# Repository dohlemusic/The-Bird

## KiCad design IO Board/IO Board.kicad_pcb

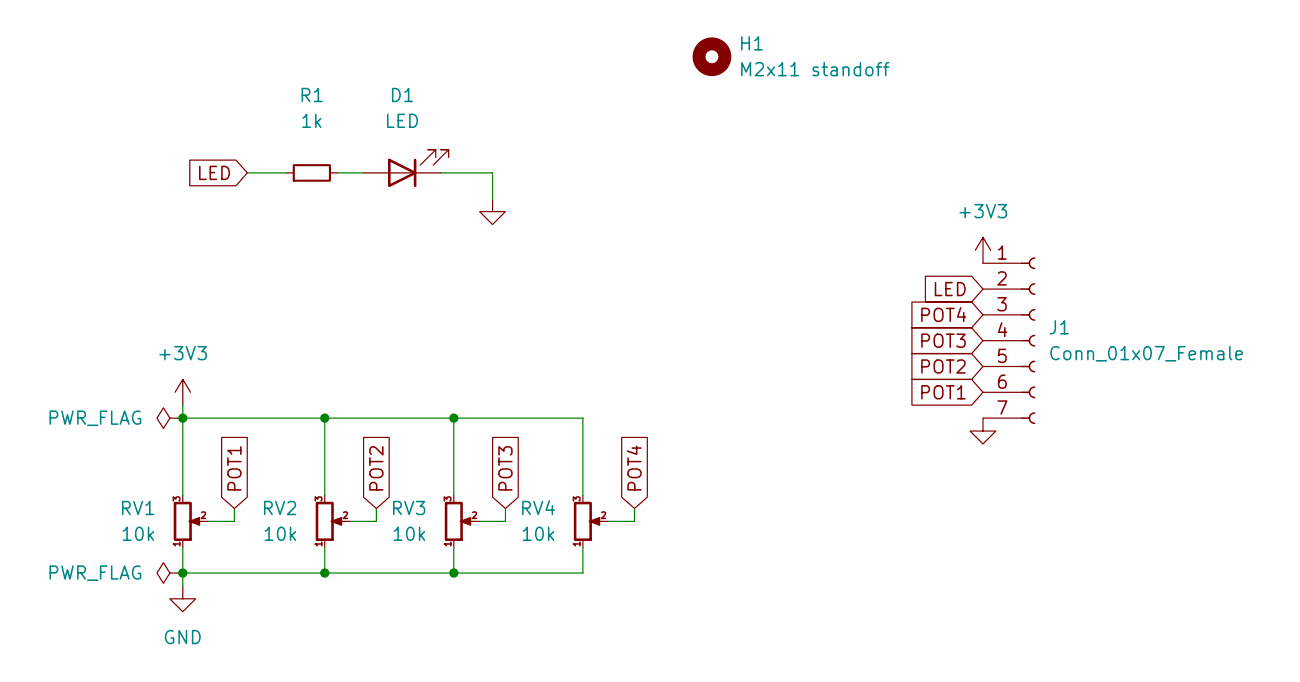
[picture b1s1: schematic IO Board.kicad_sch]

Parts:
D1: LED; LED_D3.0mm
H1: M2x11 standoff; MountingHole_2.2mm_M2
J1: Conn_01x07_Female; PinHeader_1x07_P2.54mm_Vertical
R1: 1k; R_Axial_DIN0207_L6.3mm_D2.5mm_P10.16mm_Horizontal
RV1, RV2, RV3, RV4: 10k; RK09L1140A5P

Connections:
+3V3: J1.1, RV1.3, RV2.3, RV3.3, RV4.3
GND: D1.1 (K), J1.7, RV1.1, RV2.1, RV3.1, RV4.1
LED: J1.2, R1.1
unnamed: D1.2 (A), R1.2
POT1: J1.6, RV1.2
POT2: J1.5, RV2.2
POT3: J1.4, RV3.2
POT4: J1.3, RV4.2

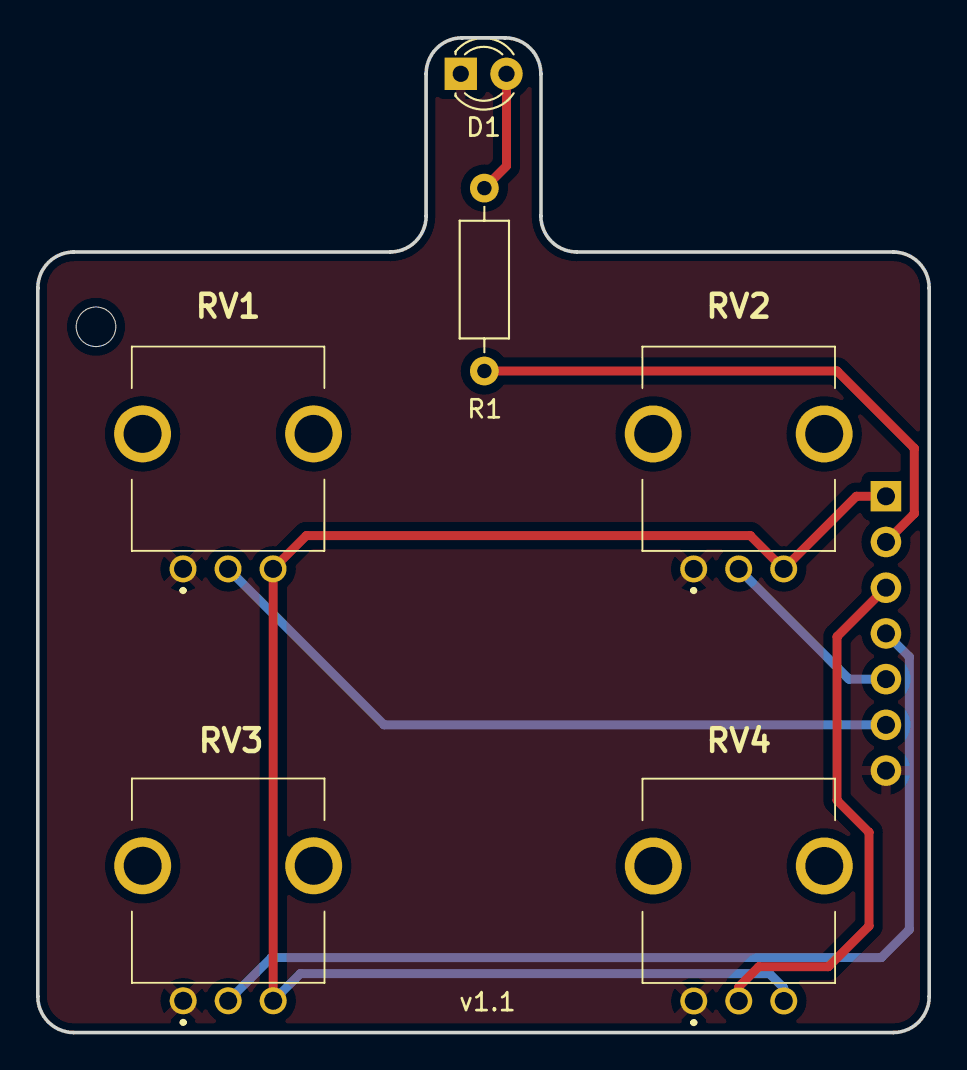
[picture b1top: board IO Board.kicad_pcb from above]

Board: 2 copper layers, 49.5 x 55.3 mm, 8 parts (1 on the bottom side), 8 nets.

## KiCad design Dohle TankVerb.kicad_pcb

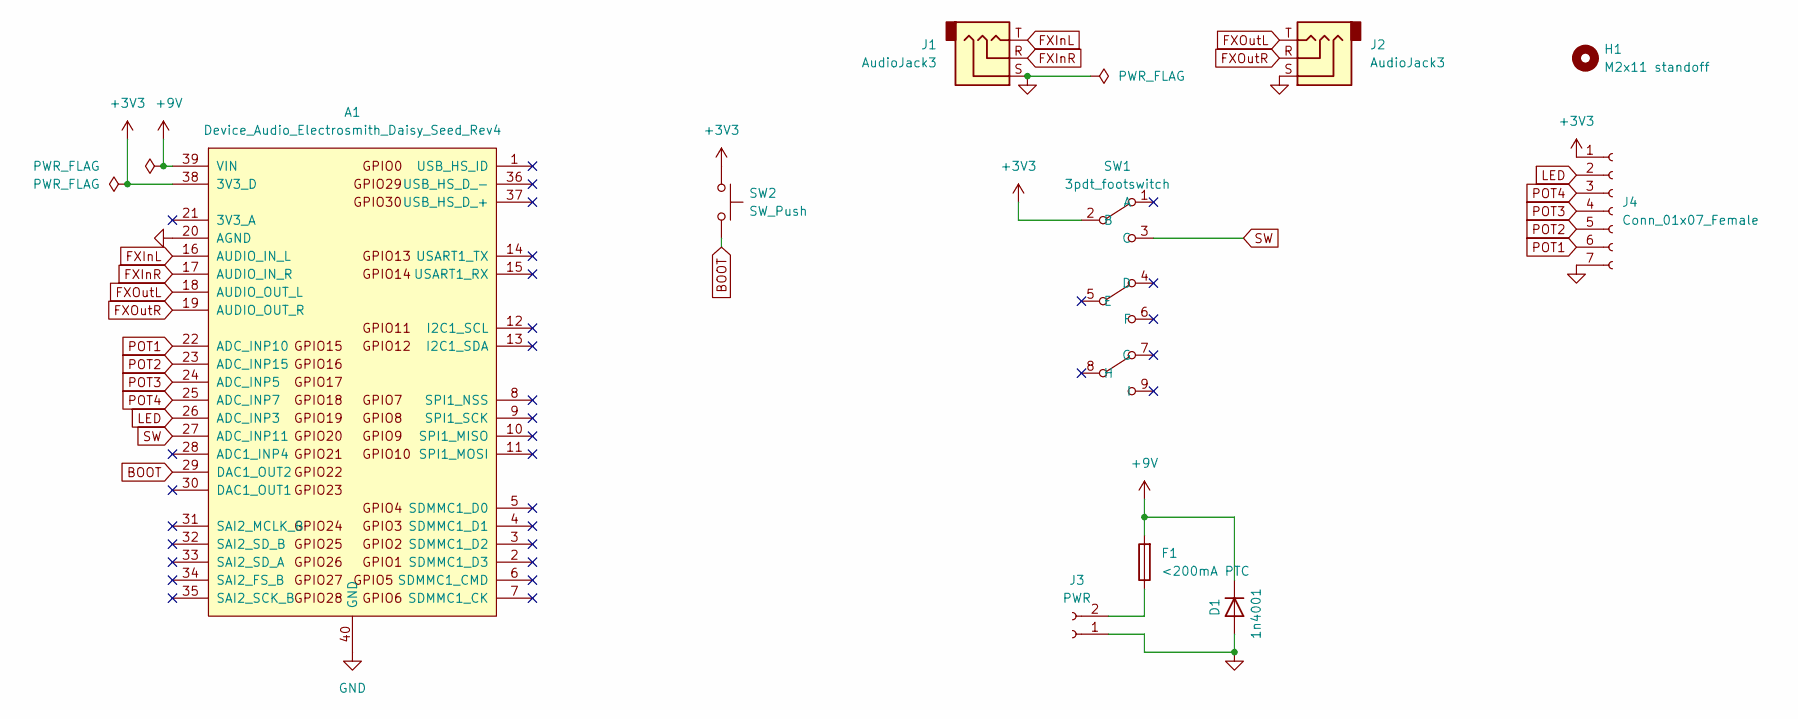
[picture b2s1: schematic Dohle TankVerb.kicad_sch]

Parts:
A1: Device_Audio_Electrosmith_Daisy_Seed_Rev4; Device_Audio_Electrosmith_Daisy_Seed
D1: 1n4001; D_DO-15_P12.70mm_Horizontal
F1: <200mA PTC; C_Rect_L7.0mm_W4.5mm_P5.00mm
H1: M2x11 standoff; MountingHole_2.2mm_M2
J1, J2: AudioJack3; StereoJackVertical
J3: PWR; JST_PH_B2B-PH-K_1x02_P2.00mm_Vertical
J4: Conn_01x07_Female; PinSocket_1x07_P2.54mm_Vertical
SW1: 3pdt_footswitch
SW2: SW_Push; PTS645VJM61LFS

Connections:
+3V3: A1.38 (3V3_D), J4.1, SW1.2 (B), SW2.1; also elsewhere on the board
+9V: A1.39 (VIN), D1.1 (K), F1.2
BOOT: A1.29 (DAC1_OUT2), SW2.2
EXPRESSION: A1.28 (ADC1_INP4); also elsewhere on the board
FXInL: A1.16 (AUDIO_IN_L), J1.T
FXInR: A1.17 (AUDIO_IN_R), J1.R
FXOutL: A1.18 (AUDIO_OUT_L), J2.T
FXOutR: A1.19 (AUDIO_OUT_R), J2.R
GND: A1.20 (AGND), A1.40 (GND), D1.2 (A), J1.S, J2.S, J3.1, J4.7; also elsewhere on the board
LED: A1.26 (ADC_INP3), J4.2
unnamed: F1.1, J3.2
POT1: A1.22 (ADC_INP10), J4.6
POT2: A1.23 (ADC_INP15), J4.5
POT3: A1.24 (ADC_INP5), J4.4
POT4: A1.25 (ADC_INP7), J4.3
SW: A1.27 (ADC_INP11), SW1.3 (C)

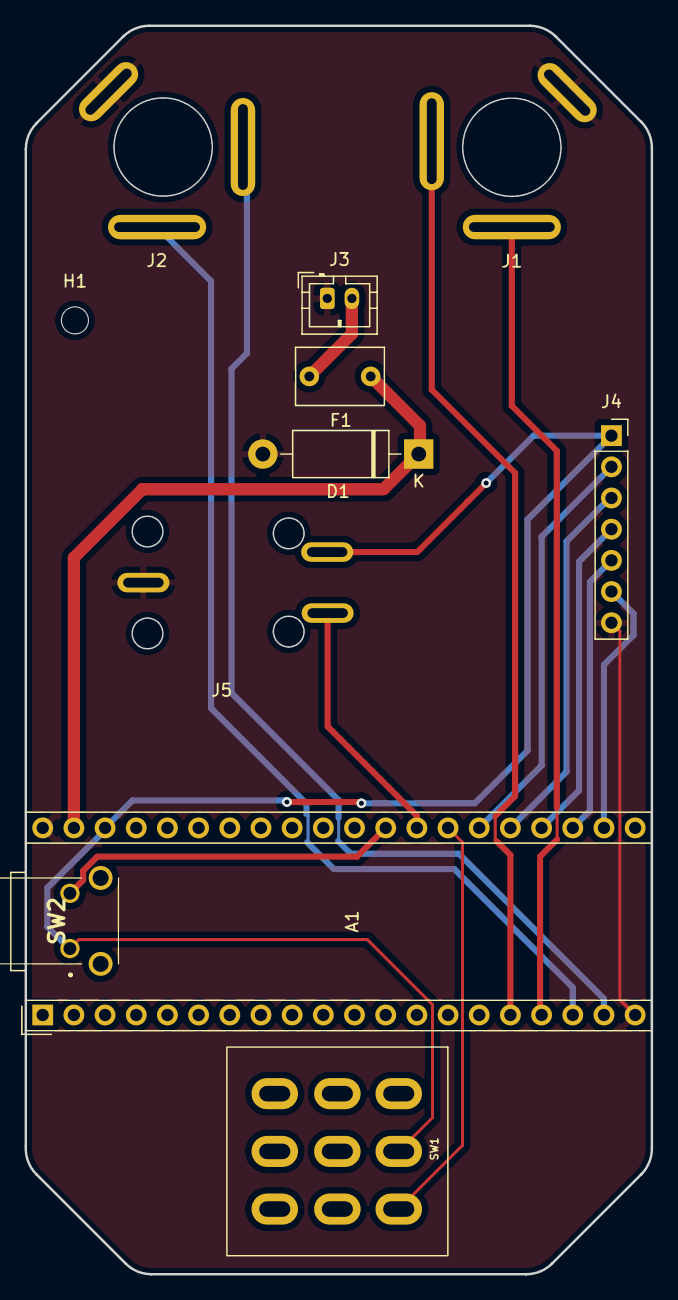
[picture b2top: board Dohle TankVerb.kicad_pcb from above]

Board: 2 copper layers, 51.0 x 101.7 mm, 11 parts (0 on the bottom side), 16 nets.

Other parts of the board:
J5: ExpressionJack

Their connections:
+3V3: J5.T; also elsewhere on the board
EXPRESSION: J5.R; also elsewhere on the board
GND: J5.S; also elsewhere on the board

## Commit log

2023-04-02 Add the first stable version of the Bird
2023-06-24 Add license
2023-06-25 Move components to make space for the pedal plug
2023-07-09 Finish adding the expression pedal. New release.
2023-07-23 Migrate everything to platformio
2023-07-23 Cleanup
2023-07-23 Update gitignore files
2023-07-23 Split headers/sources
2023-07-24 Optimize the time stretching algorithm and add support for expression pedal
2023-07-24 Fix bug with insufficient block size
2023-07-24 Use linear interpolation
    Gets rid of strange stuttering/clicking noise when a continuous sound is played through the delay line (e.g. on a synthesizer). Further optimizations required, as the AUDIO_BLOCK_SIZE is too small fo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
    TODO: Get rid of resize buffers and resize in place if possible
    TODO: Handwrite ring buffer which uses bit mask rather than expensive modulo, described in Pirckle's book on DSP effects. Currently used fractional delay isn't probably needed, as the length is fixed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
2023-07-25 Interpolate in place and use more efficient ring buffer
2023-07-25 Use faster lowpass and soft clipping
2023-07-26 Try interpolation when downsampling back to output
    note: it doesn't work well - clicking noise still present when playing a note continuously
2023-07-26 Get back to the conventional lerp with buffers
    TODO: Try to get back to the in-place version that doesn't require extra memory, but be careful not to reintroduce the clicking noises
2023-07-26 Use a compromise between interpolate in place and using buffer
2023-07-28 Fix clicking noises caused by array index out of bounds
2023-07-28 Optimize delay resizing (#3)
    Gets rid of the old algorithm that would resize the delay line itself. Thanks to this, there's no more aggressive clicking noise when the length of the delay line changes.
    Instead, the delay line has now a fixed length and the samples get time stretched (resized with linear interpolation) before feeding them to the delay line and the output of the delay line is resized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
    The above results in the same pitch shift effect as the delay "length" changes as before, but the clicking noise is eliminated.
    Unfortunately some form of "digital sounding" noise still remains at shorter delay lengths and it results either from bad interpolation of
2023-07-28 Remove dependency on arduino (WIP)
2023-07-31 Use a more clever way to improve interpolation quality at the input
2023-07-31 Get rid of one extra buffer that wasn't needed
2023-07-31 Deglitch knobs
2023-07-31 Prevent overrun of output as well as input
2023-07-31 Simplify resizeNearestNeighbor
2023-07-31 Fix clicking noises (#4)
    * Use a more clever way to improve interpolation quality at the input
    * Get rid of one extra buffer that wasn't needed
    * Deglitch knobs
    * Prevent overrun of output as well as input
    * Simplify resizeNearestNeighbor
